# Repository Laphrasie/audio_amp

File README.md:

A simple audio amplifier using LM386.
PCB is produced by pcbway

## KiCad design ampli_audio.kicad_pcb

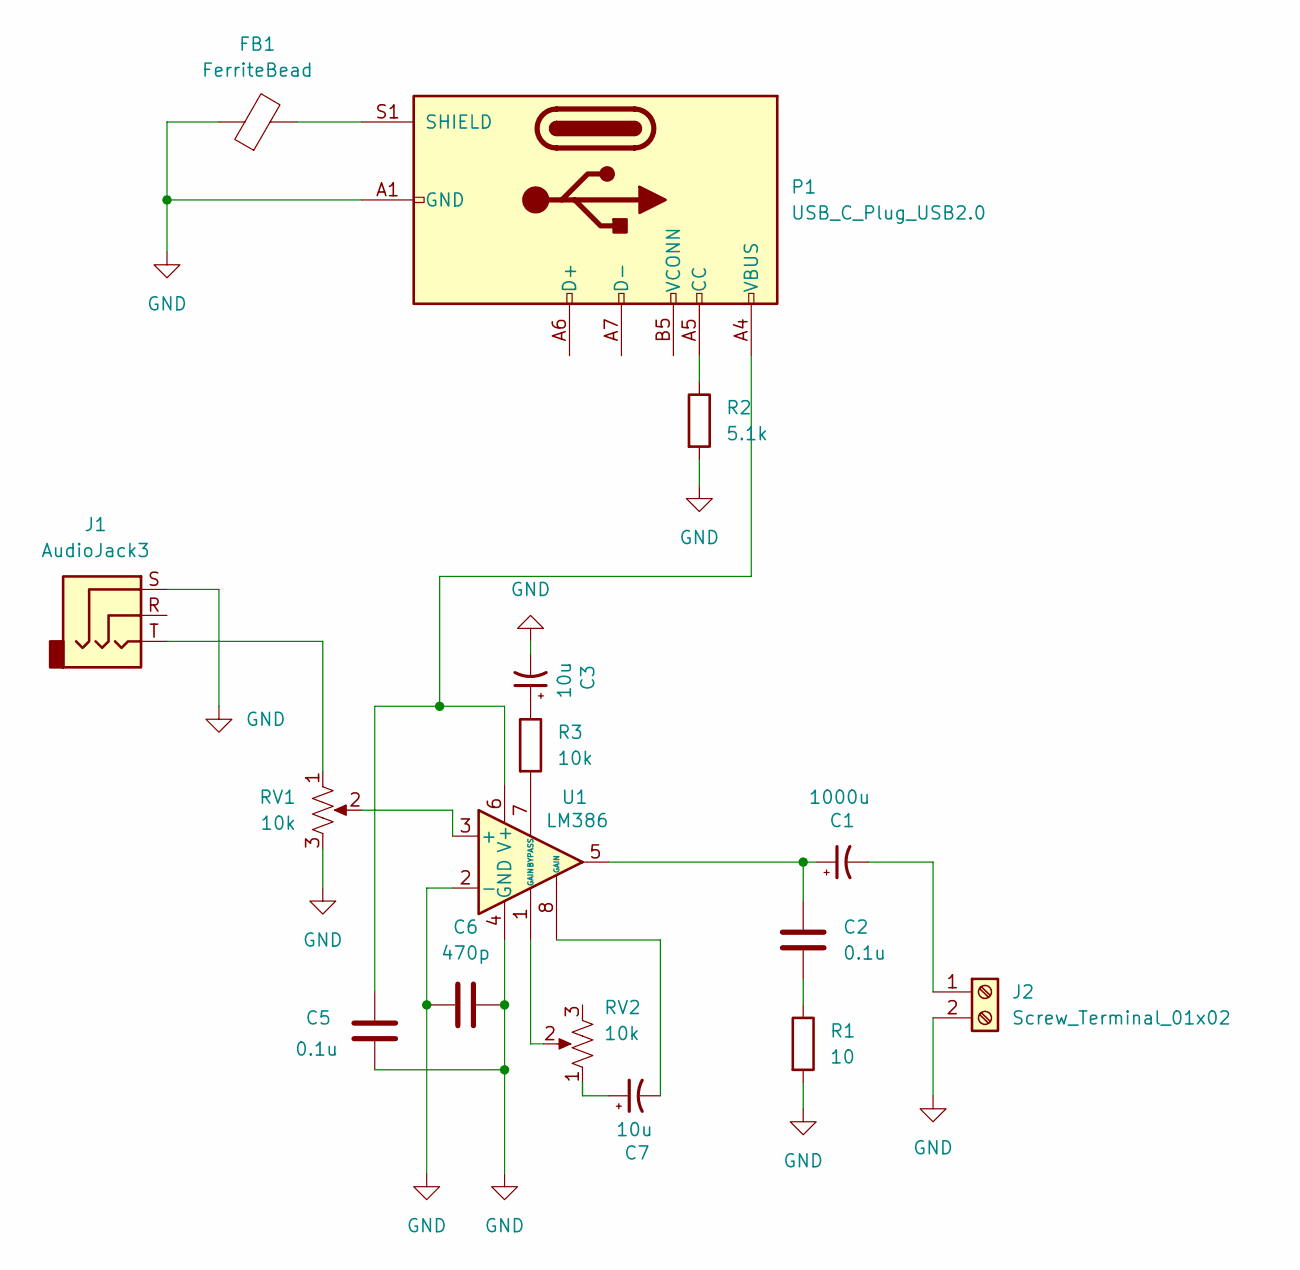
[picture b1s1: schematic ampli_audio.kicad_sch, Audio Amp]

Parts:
C1: 1000u; C_Disc_D3.0mm_W1.6mm_P2.50mm
C2, C5: 0.1u; C_0603_1608Metric_Pad1.08x0.95mm_HandSolder
C3, C7: 10u; C_Disc_D3.0mm_W1.6mm_P2.50mm
C6: 470p; C_0603_1608Metric_Pad1.08x0.95mm_HandSolder
FB1: FerriteBead; R_0201_0603Metric_Pad0.64x0.40mm_HandSolder
J1: AudioJack3; Jack_3.5mm_CUI_SJ-3523-SMT_Horizontal
J2: Screw_Terminal_01x02; TerminalBlock_4Ucon_1x02_P3.50mm_Horizontal
P1: USB_C_Plug_USB2.0; USB_C_Plug_ShenzhenJingTuoJin_918-118A2021Y40002_Vertical
R1: 10; R_0603_1608Metric_Pad0.98x0.95mm_HandSolder
R2: 5.1k; R_0603_1608Metric_Pad0.98x0.95mm_HandSolder
R3: 10k; R_0603_1608Metric_Pad0.98x0.95mm_HandSolder
RV1, RV2: 10k; Potentiometer_ACP_CA6-VSMD_Vertical
U1: LM386; DIP-8_W7.62mm_LongPads

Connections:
GND: C3.2, C5.1, C6.1, C6.2, FB1.1, J1.S, J2.2, P1.A1 (GND), P1.A12 (GND), P1.B1 (GND), P1.B12 (GND), R1.2, R2.2, RV1.3, U1.2 (-), U1.4 (GND)
unnamed: C1.1, C2.1, U1.5
unnamed: C2.2, R1.1
unnamed: C3.1, R3.1
unnamed: C7.1, RV2.1
unnamed: C7.2, U1.8 (GAIN)
unnamed: J1.T, RV1.1
unnamed: C1.2, J2.1
unnamed: P1.A5 (CC), R2.1
unnamed: FB1.2, P1.S1 (SHIELD)
unnamed: RV2.2, U1.1 (GAIN)
unnamed: RV1.2, U1.3 (+)
unnamed: R3.2, U1.7 (BYPASS)
unnamed: C5.2, P1.A4 (VBUS), P1.A9 (VBUS), P1.B4 (VBUS), P1.B9 (VBUS), U1.6 (V+)

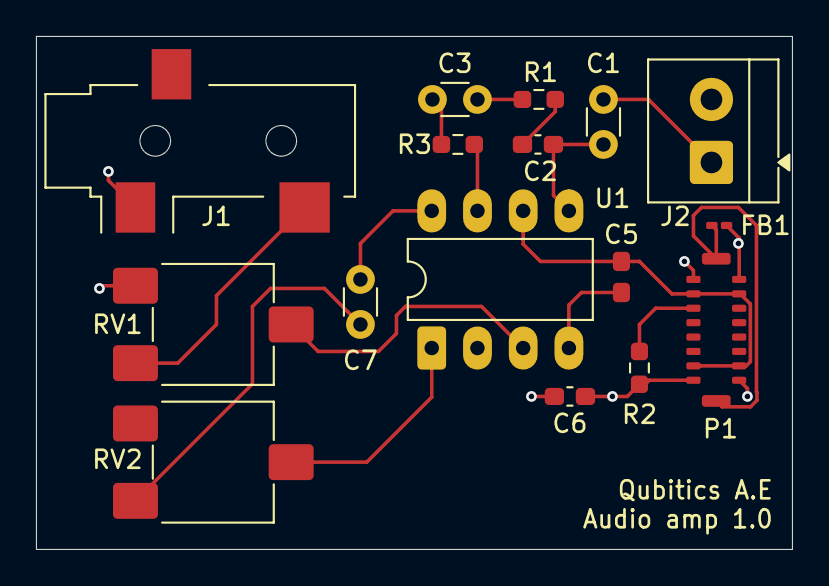
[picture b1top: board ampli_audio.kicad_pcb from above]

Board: 2 copper layers, 42.0 x 28.5 mm, 16 parts (0 on the bottom side), 14 nets.

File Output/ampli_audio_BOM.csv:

"Id";"Designator";"Footprint";"Quantity";"Designation";"Supplier and ref";
1;"J1";"Jack_3.5mm_CUI_SJ-3523-SMT_Horizontal";1;"AudioJack3";;;
2;"R1";"R_0603_1608Metric_Pad0.98x0.95mm_HandSolder";1;"10";;;
3;"RV1,RV2";"Potentiometer_ACP_CA6-VSMD_Vertical";2;"10k";;;
4;"C6";"C_0603_1608Metric_Pad1.08x0.95mm_HandSolder";1;"470p";;;
5;"C1";"C_Disc_D3.0mm_W1.6mm_P2.50mm";1;"1000u";;;
6;"C2,C5";"C_0603_1608Metric_Pad1.08x0.95mm_HandSolder";2;"0.1u";;;
7;"P1";"USB_C_Plug_ShenzhenJingTuoJin_918-118A2021Y40002_Vertical";1;"USB_C_Plug_USB2.0";;;
8;"R2";"R_0603_1608Metric_Pad0.98x0.95mm_HandSolder";1;"5.1k";;;
9;"C3,C7";"C_Disc_D3.0mm_W1.6mm_P2.50mm";2;"10u";;;
10;"R3";"R_0603_1608Metric_Pad0.98x0.95mm_HandSolder";1;"10k";;;
11;"FB1";"R_0201_0603Metric_Pad0.64x0.40mm_HandSolder";1;"FerriteBead";;;
12;"U1";"DIP-8_W7.62mm_LongPads";1;"LM386";;;
13;"J2";"TerminalBlock_4Ucon_1x02_P3.50mm_Horizontal";1;"Screw_Terminal_01x02";;;
